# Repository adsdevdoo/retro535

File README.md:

# retro535

**Siemens SAB80535-N Retro Development Board v1.0** — плата 100 × 80 мм,
два слоя, съёмный SAB80535-N в THT-панели PLCC-68, 64 КиБ доступного CODE
во внешней Flash и отдельные 32 КиБ SRAM. Питание USB-C; FT232RL UART,
RESET, пользовательский LED P4.0, разъёмы GPIO/аналоговых входов/шины.

**Статус: инженерный прототип, не испытан в железе.** Производственный архив
для первой пробной партии — `fabrication/retro535-v1.0-jlcpcb.zip`.
Контрольные результаты и границы проверки — `reports/release-review.md`.
Покупку, загрузку файлов и заказ в JLCPCB выполняет владелец платы.

## Открыть проект

Открыть `hardware/retro535.kicad_pro` в **KiCad 9.0.2 или новее**.
Главная схема `retro535.kicad_sch` включает ещё три редактируемых листа.
Плата `retro535.kicad_pcb` полностью разведена. Локальные символы,
footprints и 3D находятся рядом; сохранять структуру каталогов.

- [Архитектура, карта памяти, уровни и временной бюджет](docs/architecture.md)
- [Распиновка МК, разъёмов и контрольных точек](docs/pinout.md)
- [Сборка, первая прошивка и первое включение](docs/bring-up.md)
- [Параметры заказа JLCPCB](docs/manufacturing.md)
- [BOM с артикулами](docs/BOM.csv)
- [Схема PDF](docs/schematic.pdf)
- [Прошивка, сборка и бесплатная симуляция](firmware/README.md)
- [Datasheet и источники](docs/sources.md)
- [3D-модели и их ограничения](docs/models.md)

## Перед заказом и включением

МК ROMless: встроенного UART-загрузчика нет. USB-UART **не программатор**.
Первую прошивку и все обновления v1.0 записывают внешним программатором
в снятую SST39SF010A при полностью отключённой плате. Flash WE# на плате
заблокирован высоким уровнем; верхние 64 КиБ её 128-КиБ массива не используются.

JP1 сначала открыт: FT_PROG должен настроить USB bus-powered 500 mA,
CBUS3=PWREN# и pull-down on suspend. Основная часть включается после
enumeration; от зарядки без USB-хоста автономного старта нет. Под нагрузкой
нужно **>4,75 В на TP3**; слабый порт/длинный кабель может оставить МК в RESET.
GPIO — 5 В TTL. Периферию не подключать до успешного теста SRAM.

## Проверки и воспроизводимость

Схема создана из `tools/design.py`; `tools/generate.py` обновляет схему,
BOM и правила проекта, сохраняя отредактированную локальную библиотеку.
**Не запускать make_board.py/finish_board.py/polish_board.py на финальном
PCB:** это этапы построения, они могут затереть готовую разводку.
Для новой разводки использовать отдельную копию проекта.

`tools/sync_board_metadata.py` назначает служебные NC-цепи из актуального
`reports/netlist.xml` и синхронизирует библиотеку с проверенной геометрией.
`tools/audit_models.py` проверяет все файлы 3D. `tools/audit_manufacturing.py`
независимо проверяет Gerber/Drill и собирает ZIP; ему нужен `gerbonara`
и свежий `reports/pcb-geometry.json` из `tools/export_geometry.py` (KiCad Python). CLI KiCad, работающие с одним проектом,
запускать последовательно: они могут сохранять настройки даже при экспорте.

3D-рендеры показывают пустые панели U1/U3/U4. Панель PLCC и F1 — условные
модели; внешность не доказывает точную механику. На PCB присутствуют все
68 контактов U1 независимо от упрощений STEP.

GitHub: [adsdevdoo/retro535](https://github.com/adsdevdoo/retro535).
Инструкция SSH/plink для этой Windows-машины сохранена в `AGENTS.md`.
Сторонние 3D-модели сохраняют собственные лицензии; см. `docs/models.md`.

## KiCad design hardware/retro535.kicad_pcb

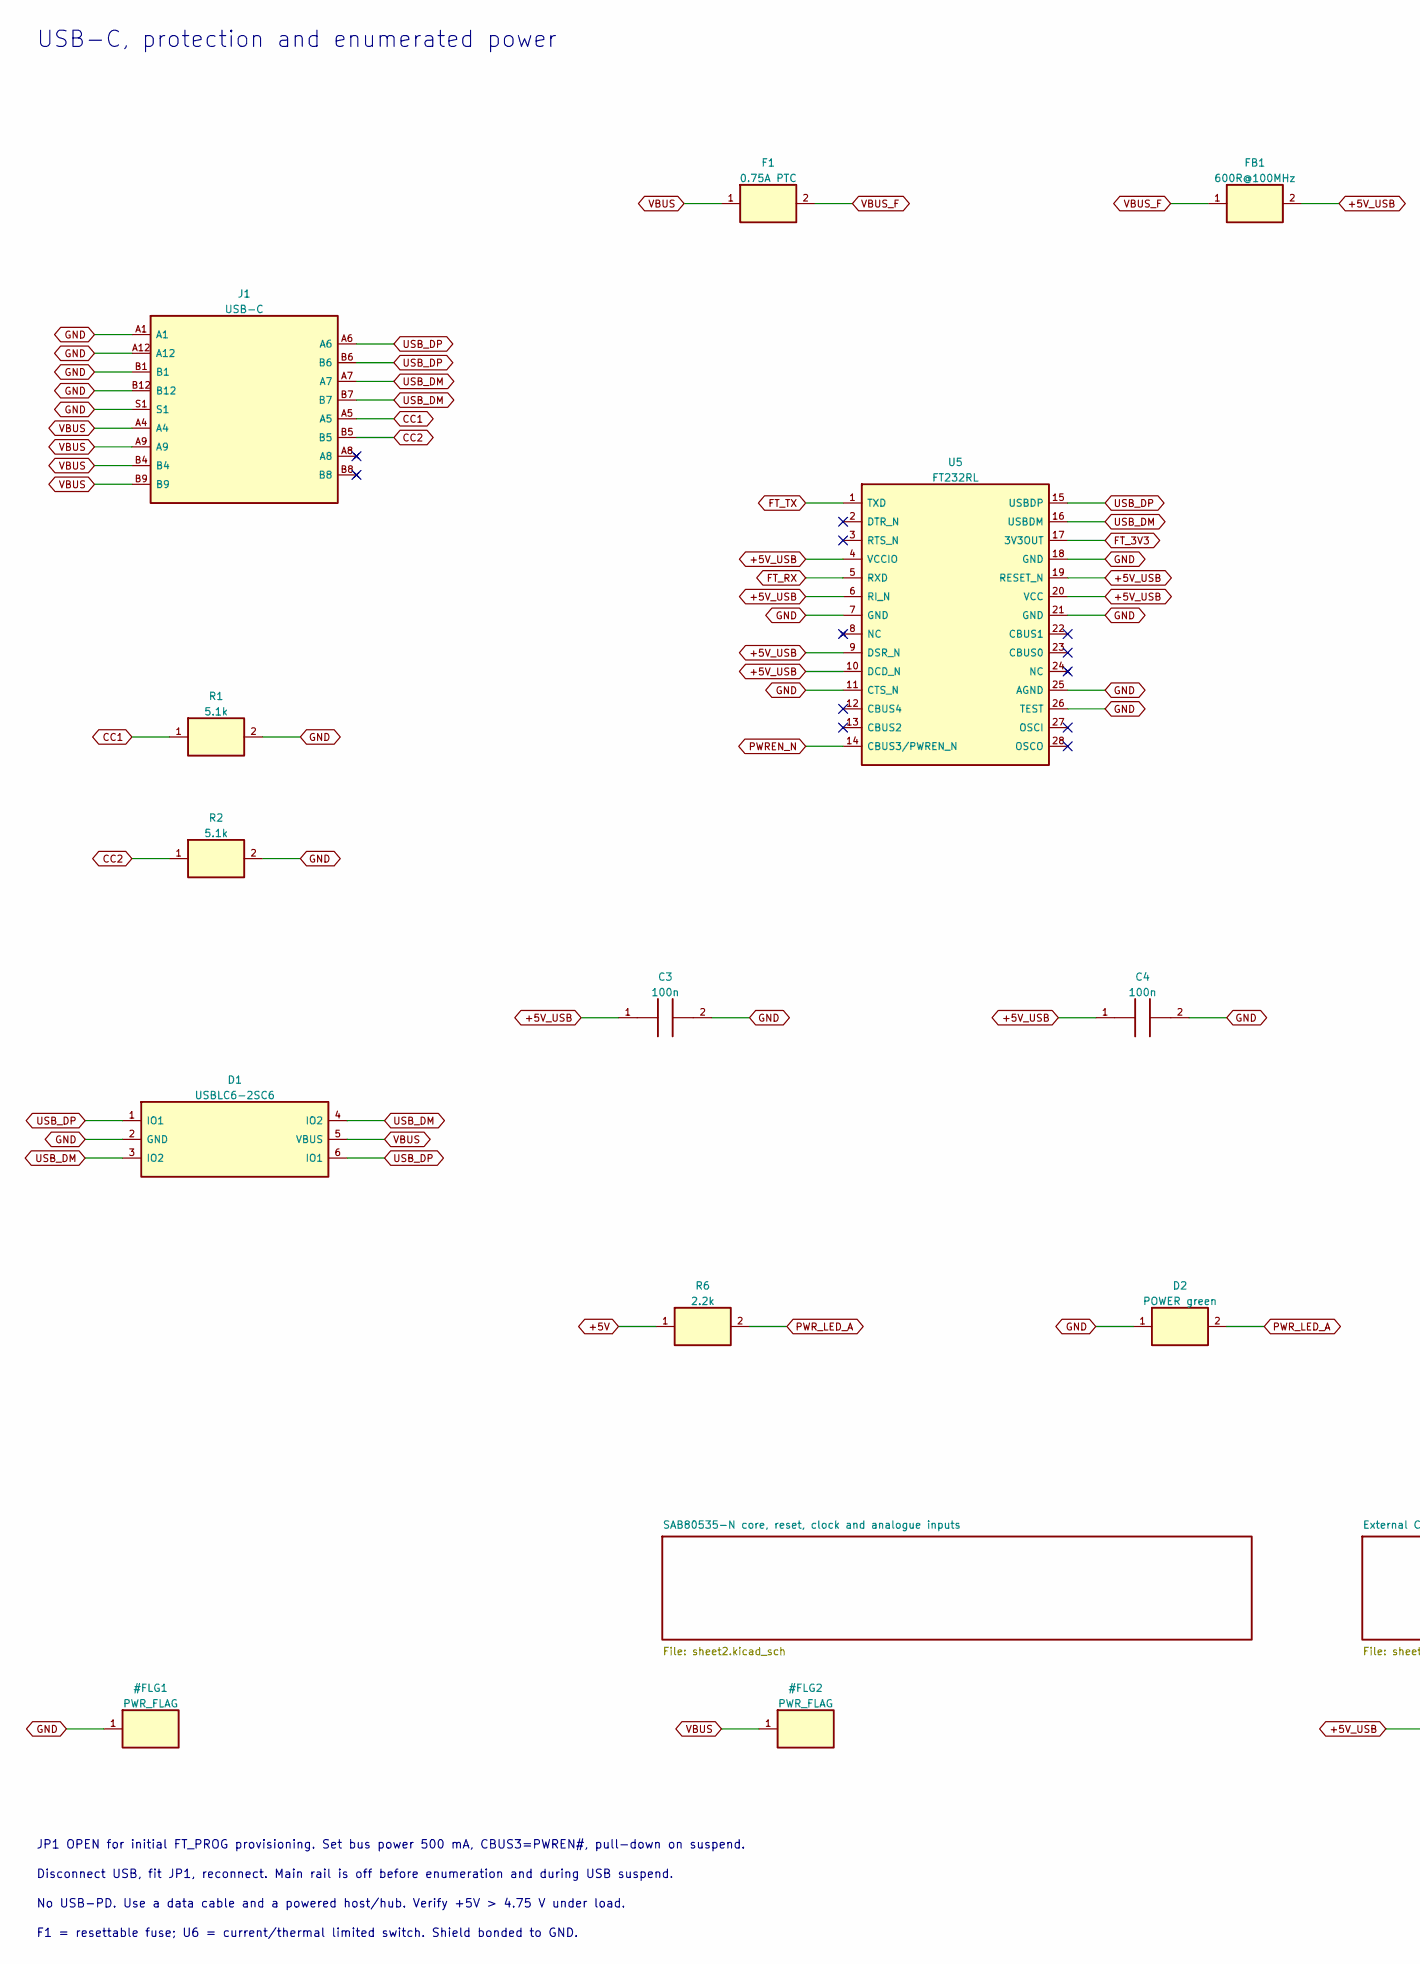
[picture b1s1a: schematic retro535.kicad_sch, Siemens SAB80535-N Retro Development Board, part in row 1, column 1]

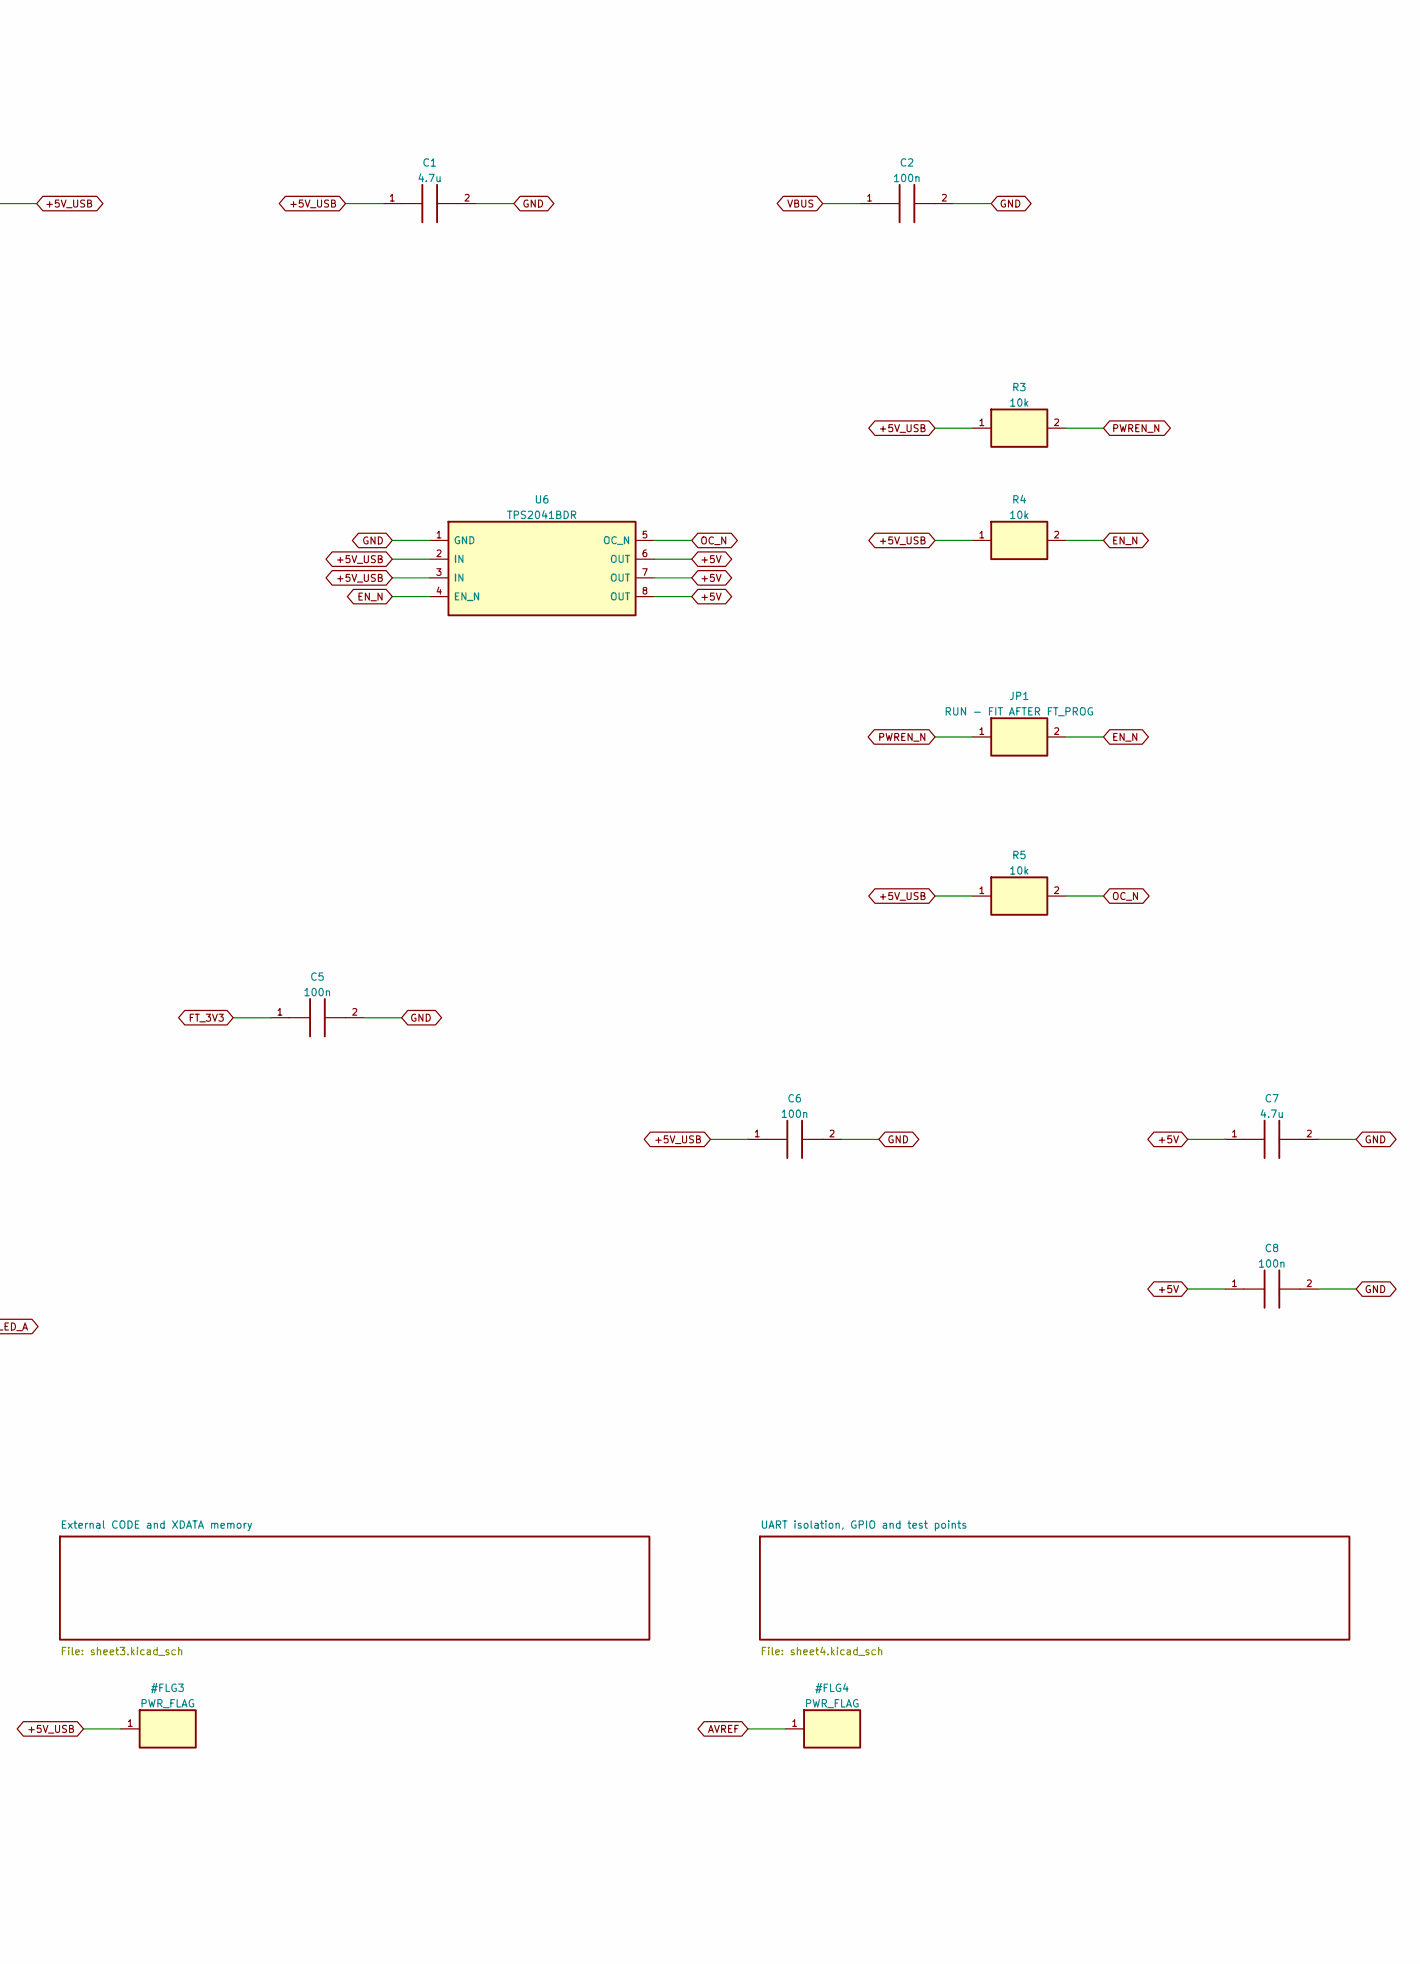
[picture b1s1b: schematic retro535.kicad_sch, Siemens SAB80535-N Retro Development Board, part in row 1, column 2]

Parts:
C1, C7: 4.7u; C_0805_2012Metric_Pad1.18x1.45mm_HandSolder; MPN GRM21BR61C475KA73L
C2, C3, C4, C5, C6, C8: 100n; C_0805_2012Metric_Pad1.18x1.45mm_HandSolder; MPN GRM21BR71H104KA01L
D1: USBLC6-2SC6; SOT-23-6; MPN USBLC6-2SC6
D2: POWER green; LED_0805_2012Metric_Pad1.15x1.40mm_HandSolder; MPN LTST-C170KGKT
F1: 0.75A PTC; Fuse_1812_4532Metric; MPN MF-MSMF075-2
FB1: 600R@100MHz; L_0805_2012Metric_Pad1.15x1.40mm_HandSolder; MPN BLM21PG601SN1D
J1: USB-C; USB_C_Receptacle_HRO_TYPE-C-31-M-12; MPN TYPE-C-31-M-12
JP1: RUN - FIT AFTER FT_PROG; PinHeader_1x02_P2.54mm_Vertical; MPN M20-9990245
R1, R2: 5.1k; R_0805_2012Metric_Pad1.20x1.40mm_HandSolder; MPN RC0805FR-075K1L
R3, R4, R5: 10k; R_0805_2012Metric_Pad1.20x1.40mm_HandSolder; MPN RC0805FR-0710KL
R6: 2.2k; R_0805_2012Metric_Pad1.20x1.40mm_HandSolder; MPN RC0805FR-072K2L
U5: FT232RL; SSOP-28_5.3x10.2mm_P0.65mm; MPN FT232RL
U6: TPS2041BDR; SOIC-8_3.9x4.9mm_P1.27mm; MPN TPS2041BDR

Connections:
+5V: C7.1, C8.1, R6.1, U6.6 (OUT), U6.7 (OUT), U6.8 (OUT); also elsewhere on the board
+5V_USB: C1.1, C3.1, C4.1, C6.1, FB1.2, R3.1, R4.1, R5.1, U5.4 (VCCIO), U5.6 (RI_N), U5.9 (DSR_N), U5.10 (DCD_N), U5.19 (RESET_N), U5.20 (VCC), U6.2 (IN), U6.3 (IN); also elsewhere on the board
CC1: J1.A5, R1.1
CC2: J1.B5, R2.1
EN_N: JP1.2, R4.2, U6.4 (EN_N)
FT_3V3: C5.1, U5.17 (3V3OUT)
FT_RX: U5.5 (RXD); also elsewhere on the board
FT_TX: U5.1 (TXD); also elsewhere on the board
GND: C1.2, C2.2, C3.2, C4.2, C5.2, C6.2, C7.2, C8.2, D1.2 (GND), D2.1, J1.A1, J1.A12, J1.B1, J1.B12, J1.S1, R1.2, R2.2, U5.7 (GND), U5.11 (CTS_N), U5.18 (GND), U5.21 (GND), U5.25 (AGND), U5.26 (TEST), U6.1 (GND); also elsewhere on the board
OC_N: R5.2, U6.5 (OC_N); also elsewhere on the board
PWREN_N: JP1.1, R3.2, U5.14 (CBUS3/PWREN_N)
PWR_LED_A: D2.2, R6.2
USB_DM: D1.3 (IO2), D1.4 (IO2), J1.A7, J1.B7, U5.16 (USBDM)
USB_DP: D1.1 (IO1), D1.6 (IO1), J1.A6, J1.B6, U5.15 (USBDP)
VBUS: C2.1, D1.5 (VBUS), F1.1, J1.A4, J1.A9, J1.B4, J1.B9
VBUS_F: F1.2, FB1.1

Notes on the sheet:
USB-C, protection and enumerated power
JP1 OPEN for initial FT_PROG provisioning. Set bus power 500 mA, CBUS3=PWREN#, pull-down on suspend.
Disconnect USB, fit JP1, reconnect. Main rail is off before enumeration and during USB suspend.
No USB-PD. Use a data cable and a powered host/hub. Verify +5V > 4.75 V under load.
F1 = resettable fuse; U6 = current/thermal limited switch. Shield bonded to GND.

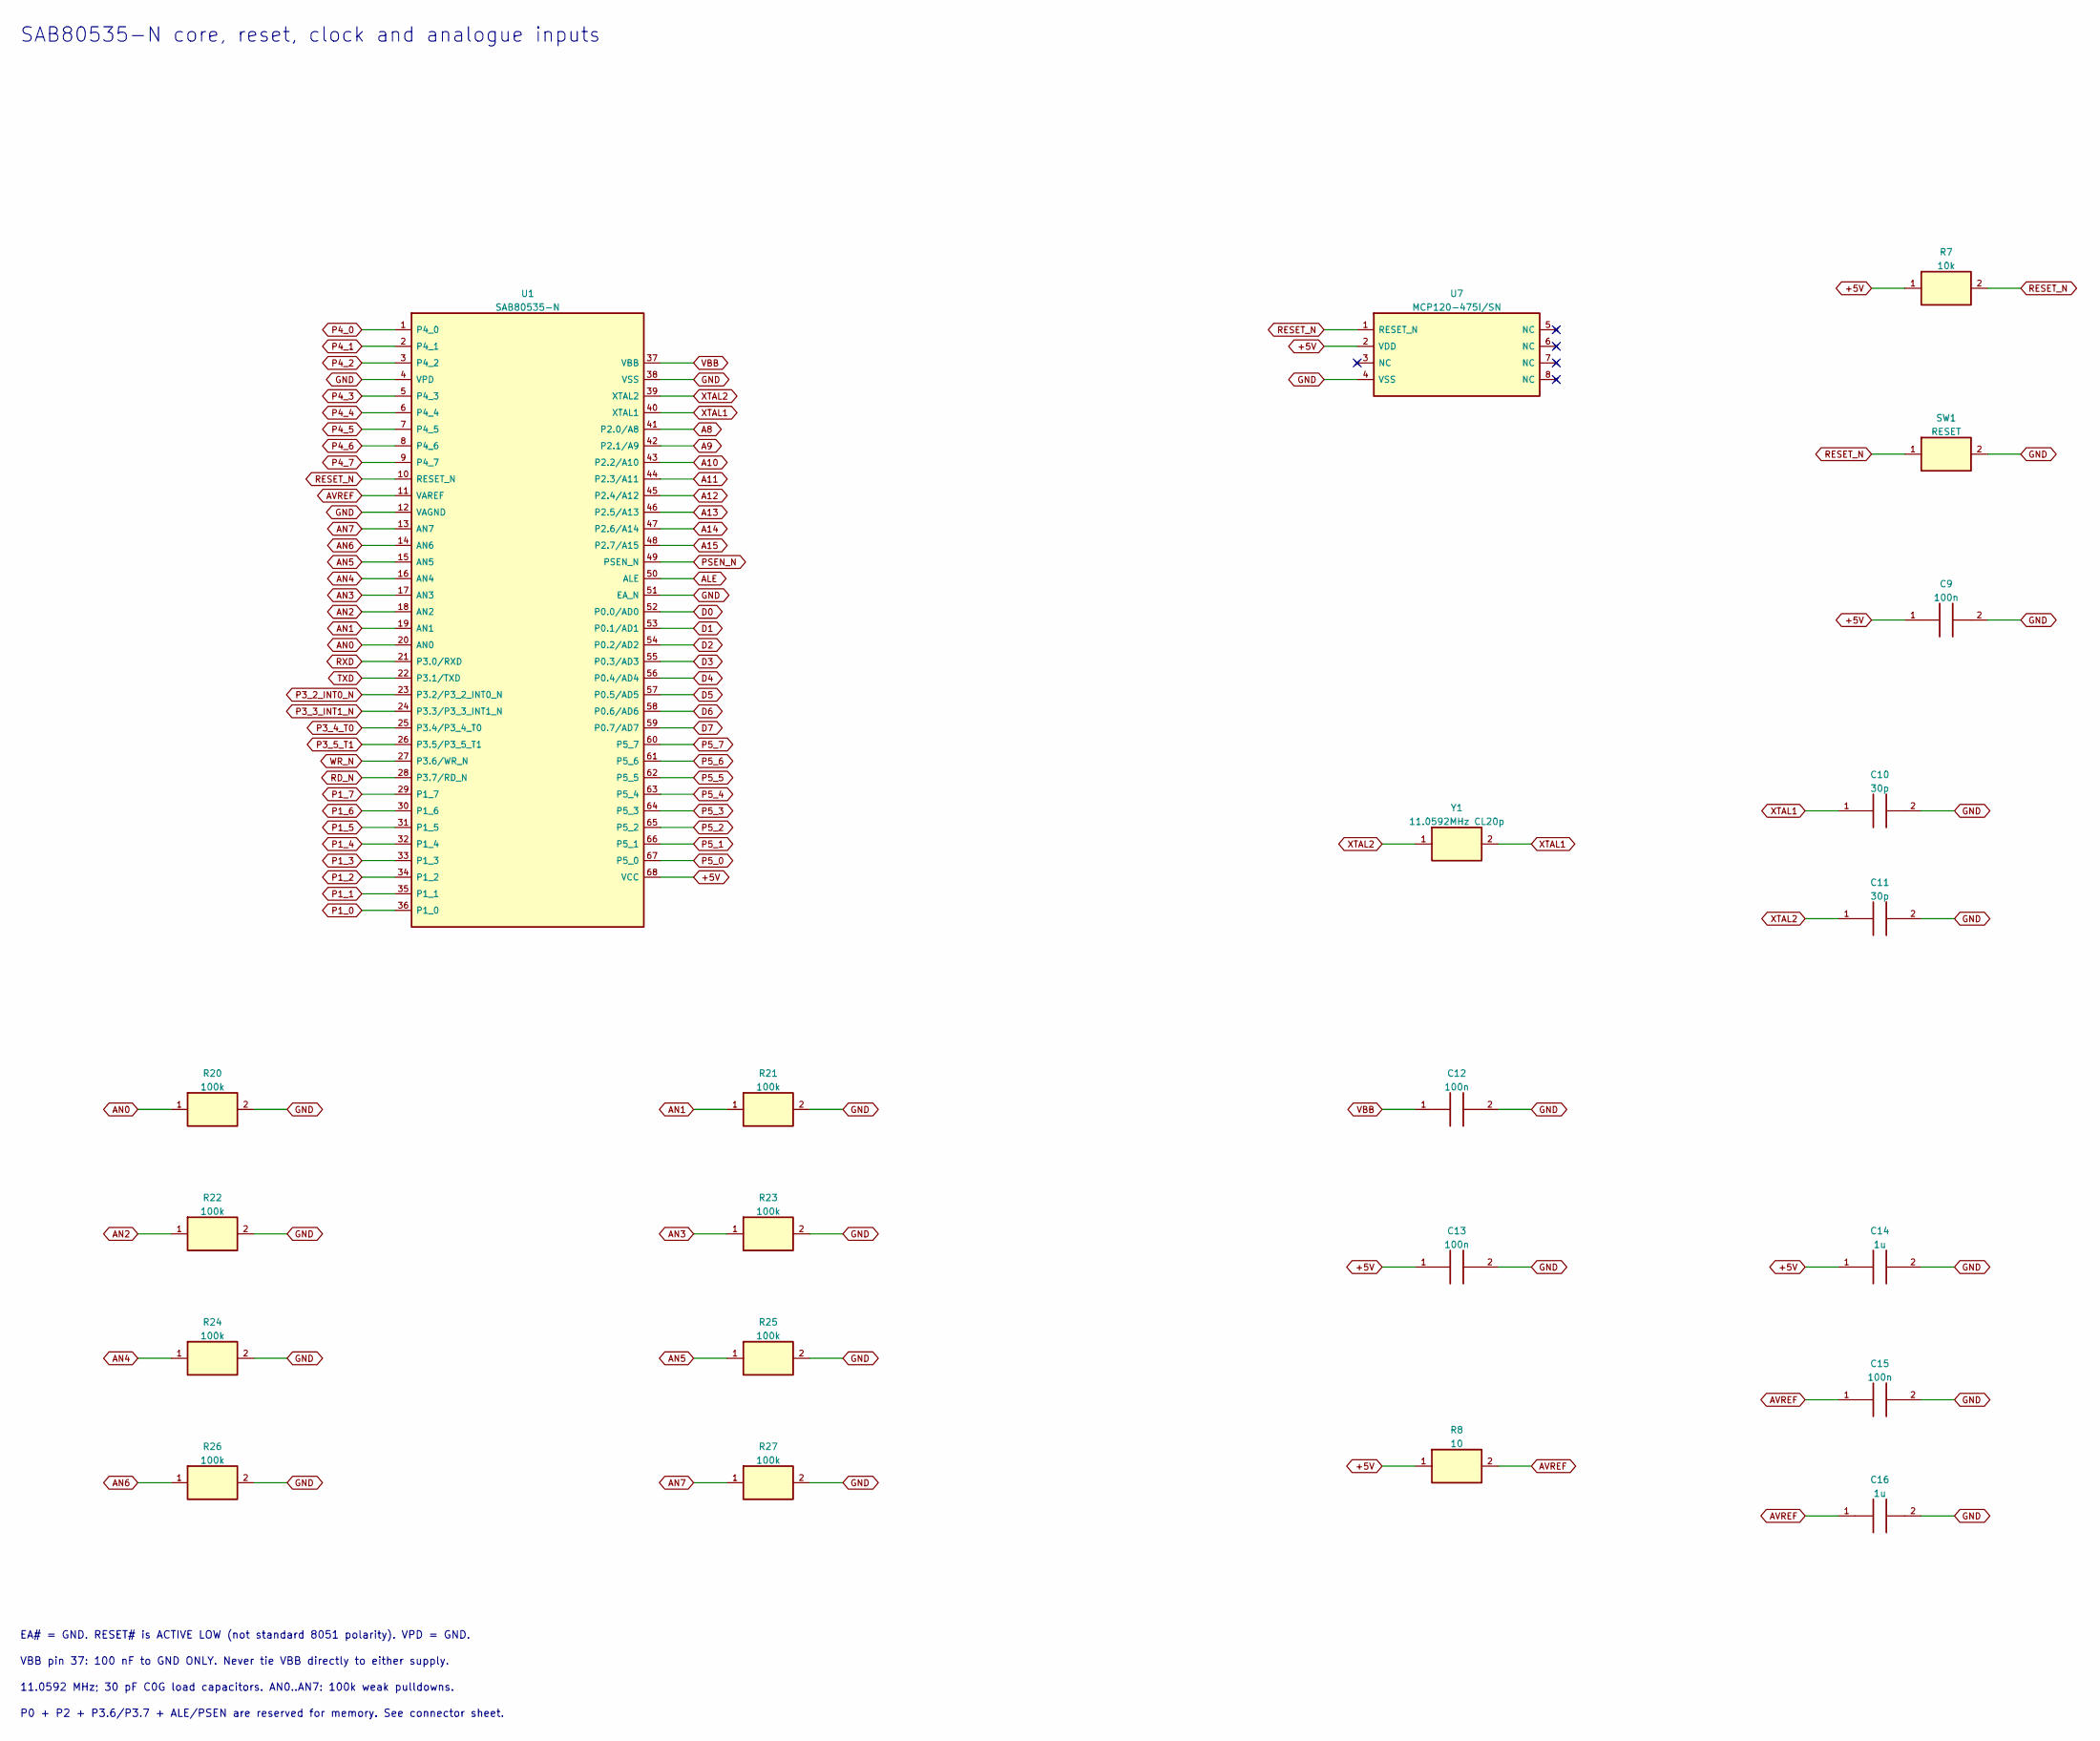
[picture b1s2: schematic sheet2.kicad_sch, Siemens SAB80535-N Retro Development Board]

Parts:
C9, C12, C13, C15: 100n; C_0805_2012Metric_Pad1.18x1.45mm_HandSolder; MPN GRM21BR71H104KA01L
C10, C11: 30p; C_0805_2012Metric_Pad1.18x1.45mm_HandSolder; MPN GRM2165C1H300JA01D
C14, C16: 1u; C_0805_2012Metric_Pad1.18x1.45mm_HandSolder; MPN GRM21BR71C105KA01L
R7: 10k; R_0805_2012Metric_Pad1.20x1.40mm_HandSolder; MPN RC0805FR-0710KL
R8: 10; R_0805_2012Metric_Pad1.20x1.40mm_HandSolder; MPN RC0805FR-0710RL
R20, R21, R22, R23, R24, R25, R26, R27: 100k; R_0805_2012Metric_Pad1.20x1.40mm_HandSolder; MPN RC0805FR-07100KL
SW1: RESET; SW_PUSH_6mm; MPN B3F-1000
U1: SAB80535-N; PLCC68_PreciDip_540-99-068-24-000-1; MPN SAB80535-N
U7: MCP120-475I/SN; SOIC-8_3.9x4.9mm_P1.27mm; MPN MCP120-475I/SN
Y1: 11.0592MHz CL20p; Crystal_HC49-U_Vertical; MPN ECS-110.5-20-4X

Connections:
+5V: C9.1, C13.1, C14.1, R7.1, R8.1, U1.68 (VCC), U7.2 (VDD); also elsewhere on the board
A8: U1.41 (P2.0/A8); also elsewhere on the board
A9: U1.42 (P2.1/A9); also elsewhere on the board
A10: U1.43 (P2.2/A10); also elsewhere on the board
A11: U1.44 (P2.3/A11); also elsewhere on the board
A12: U1.45 (P2.4/A12); also elsewhere on the board
A13: U1.46 (P2.5/A13); also elsewhere on the board
A14: U1.47 (P2.6/A14); also elsewhere on the board
A15: U1.48 (P2.7/A15); also elsewhere on the board
ALE: U1.50 (ALE); also elsewhere on the board
AN0: R20.1, U1.20 (AN0); also elsewhere on the board
AN1: R21.1, U1.19 (AN1); also elsewhere on the board
AN2: R22.1, U1.18 (AN2); also elsewhere on the board
AN3: R23.1, U1.17 (AN3); also elsewhere on the board
AN4: R24.1, U1.16 (AN4); also elsewhere on the board
AN5: R25.1, U1.15 (AN5); also elsewhere on the board
AN6: R26.1, U1.14 (AN6); also elsewhere on the board
AN7: R27.1, U1.13 (AN7); also elsewhere on the board
AVREF: C15.1, C16.1, R8.2, U1.11 (VAREF); also elsewhere on the board
D0: U1.52 (P0.0/AD0); also elsewhere on the board
D1: U1.53 (P0.1/AD1); also elsewhere on the board
D2: U1.54 (P0.2/AD2); also elsewhere on the board
D3: U1.55 (P0.3/AD3); also elsewhere on the board
D4: U1.56 (P0.4/AD4); also elsewhere on the board
D5: U1.57 (P0.5/AD5); also elsewhere on the board
D6: U1.58 (P0.6/AD6); also elsewhere on the board
D7: U1.59 (P0.7/AD7); also elsewhere on the board
GND: C9.2, C10.2, C11.2, C12.2, C13.2, C14.2, C15.2, C16.2, R20.2, R21.2, R22.2, R23.2, R24.2, R25.2, R26.2, R27.2, SW1.2, U1.4 (VPD), U1.12 (VAGND), U1.38 (VSS), U1.51 (EA_N), U7.4 (VSS); also elsewhere on the board
P1_0: U1.36 (P1_0); also elsewhere on the board
P1_1: U1.35 (P1_1); also elsewhere on the board
P1_2: U1.34 (P1_2); also elsewhere on the board
P1_3: U1.33 (P1_3); also elsewhere on the board
P1_4: U1.32 (P1_4); also elsewhere on the board
P1_5: U1.31 (P1_5); also elsewhere on the board
P1_6: U1.30 (P1_6); also elsewhere on the board
P1_7: U1.29 (P1_7); also elsewhere on the board
P3_2_INT0_N: U1.23 (P3.2/P3_2_INT0_N); also elsewhere on the board
P3_3_INT1_N: U1.24 (P3.3/P3_3_INT1_N); also elsewhere on the board
P3_4_T0: U1.25 (P3.4/P3_4_T0); also elsewhere on the board
P3_5_T1: U1.26 (P3.5/P3_5_T1); also elsewhere on the board
P4_0: U1.1 (P4_0); also elsewhere on the board
P4_1: U1.2 (P4_1); also elsewhere on the board
P4_2: U1.3 (P4_2); also elsewhere on the board
P4_3: U1.5 (P4_3); also elsewhere on the board
P4_4: U1.6 (P4_4); also elsewhere on the board
P4_5: U1.7 (P4_5); also elsewhere on the board
P4_6: U1.8 (P4_6); also elsewhere on the board
P4_7: U1.9 (P4_7); also elsewhere on the board
P5_0: U1.67 (P5_0); also elsewhere on the board
P5_1: U1.66 (P5_1); also elsewhere on the board
P5_2: U1.65 (P5_2); also elsewhere on the board
P5_3: U1.64 (P5_3); also elsewhere on the board
P5_4: U1.63 (P5_4); also elsewhere on the board
P5_5: U1.62 (P5_5); also elsewhere on the board
P5_6: U1.61 (P5_6); also elsewhere on the board
P5_7: U1.60 (P5_7); also elsewhere on the board
PSEN_N: U1.49 (PSEN_N); also elsewhere on the board
RD_N: U1.28 (P3.7/RD_N); also elsewhere on the board
RESET_N: R7.2, SW1.1, U1.10 (RESET_N), U7.1 (RESET_N); also elsewhere on the board
RXD: U1.21 (P3.0/RXD); also elsewhere on the board
TXD: U1.22 (P3.1/TXD); also elsewhere on the board
VBB: C12.1, U1.37 (VBB)
WR_N: U1.27 (P3.6/WR_N); also elsewhere on the board
XTAL1: C10.1, U1.40 (XTAL1), Y1.2
XTAL2: C11.1, U1.39 (XTAL2), Y1.1

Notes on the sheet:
SAB80535-N core, reset, clock and analogue inputs
EA# = GND. RESET# is ACTIVE LOW (not standard 8051 polarity). VPD = GND.
VBB pin 37: 100 nF to GND ONLY. Never tie VBB directly to either supply.
11.0592 MHz; 30 pF C0G load capacitors. AN0..AN7: 100k weak pulldowns.
P0 + P2 + P3.6/P3.7 + ALE/PSEN are reserved for memory. See connector sheet.

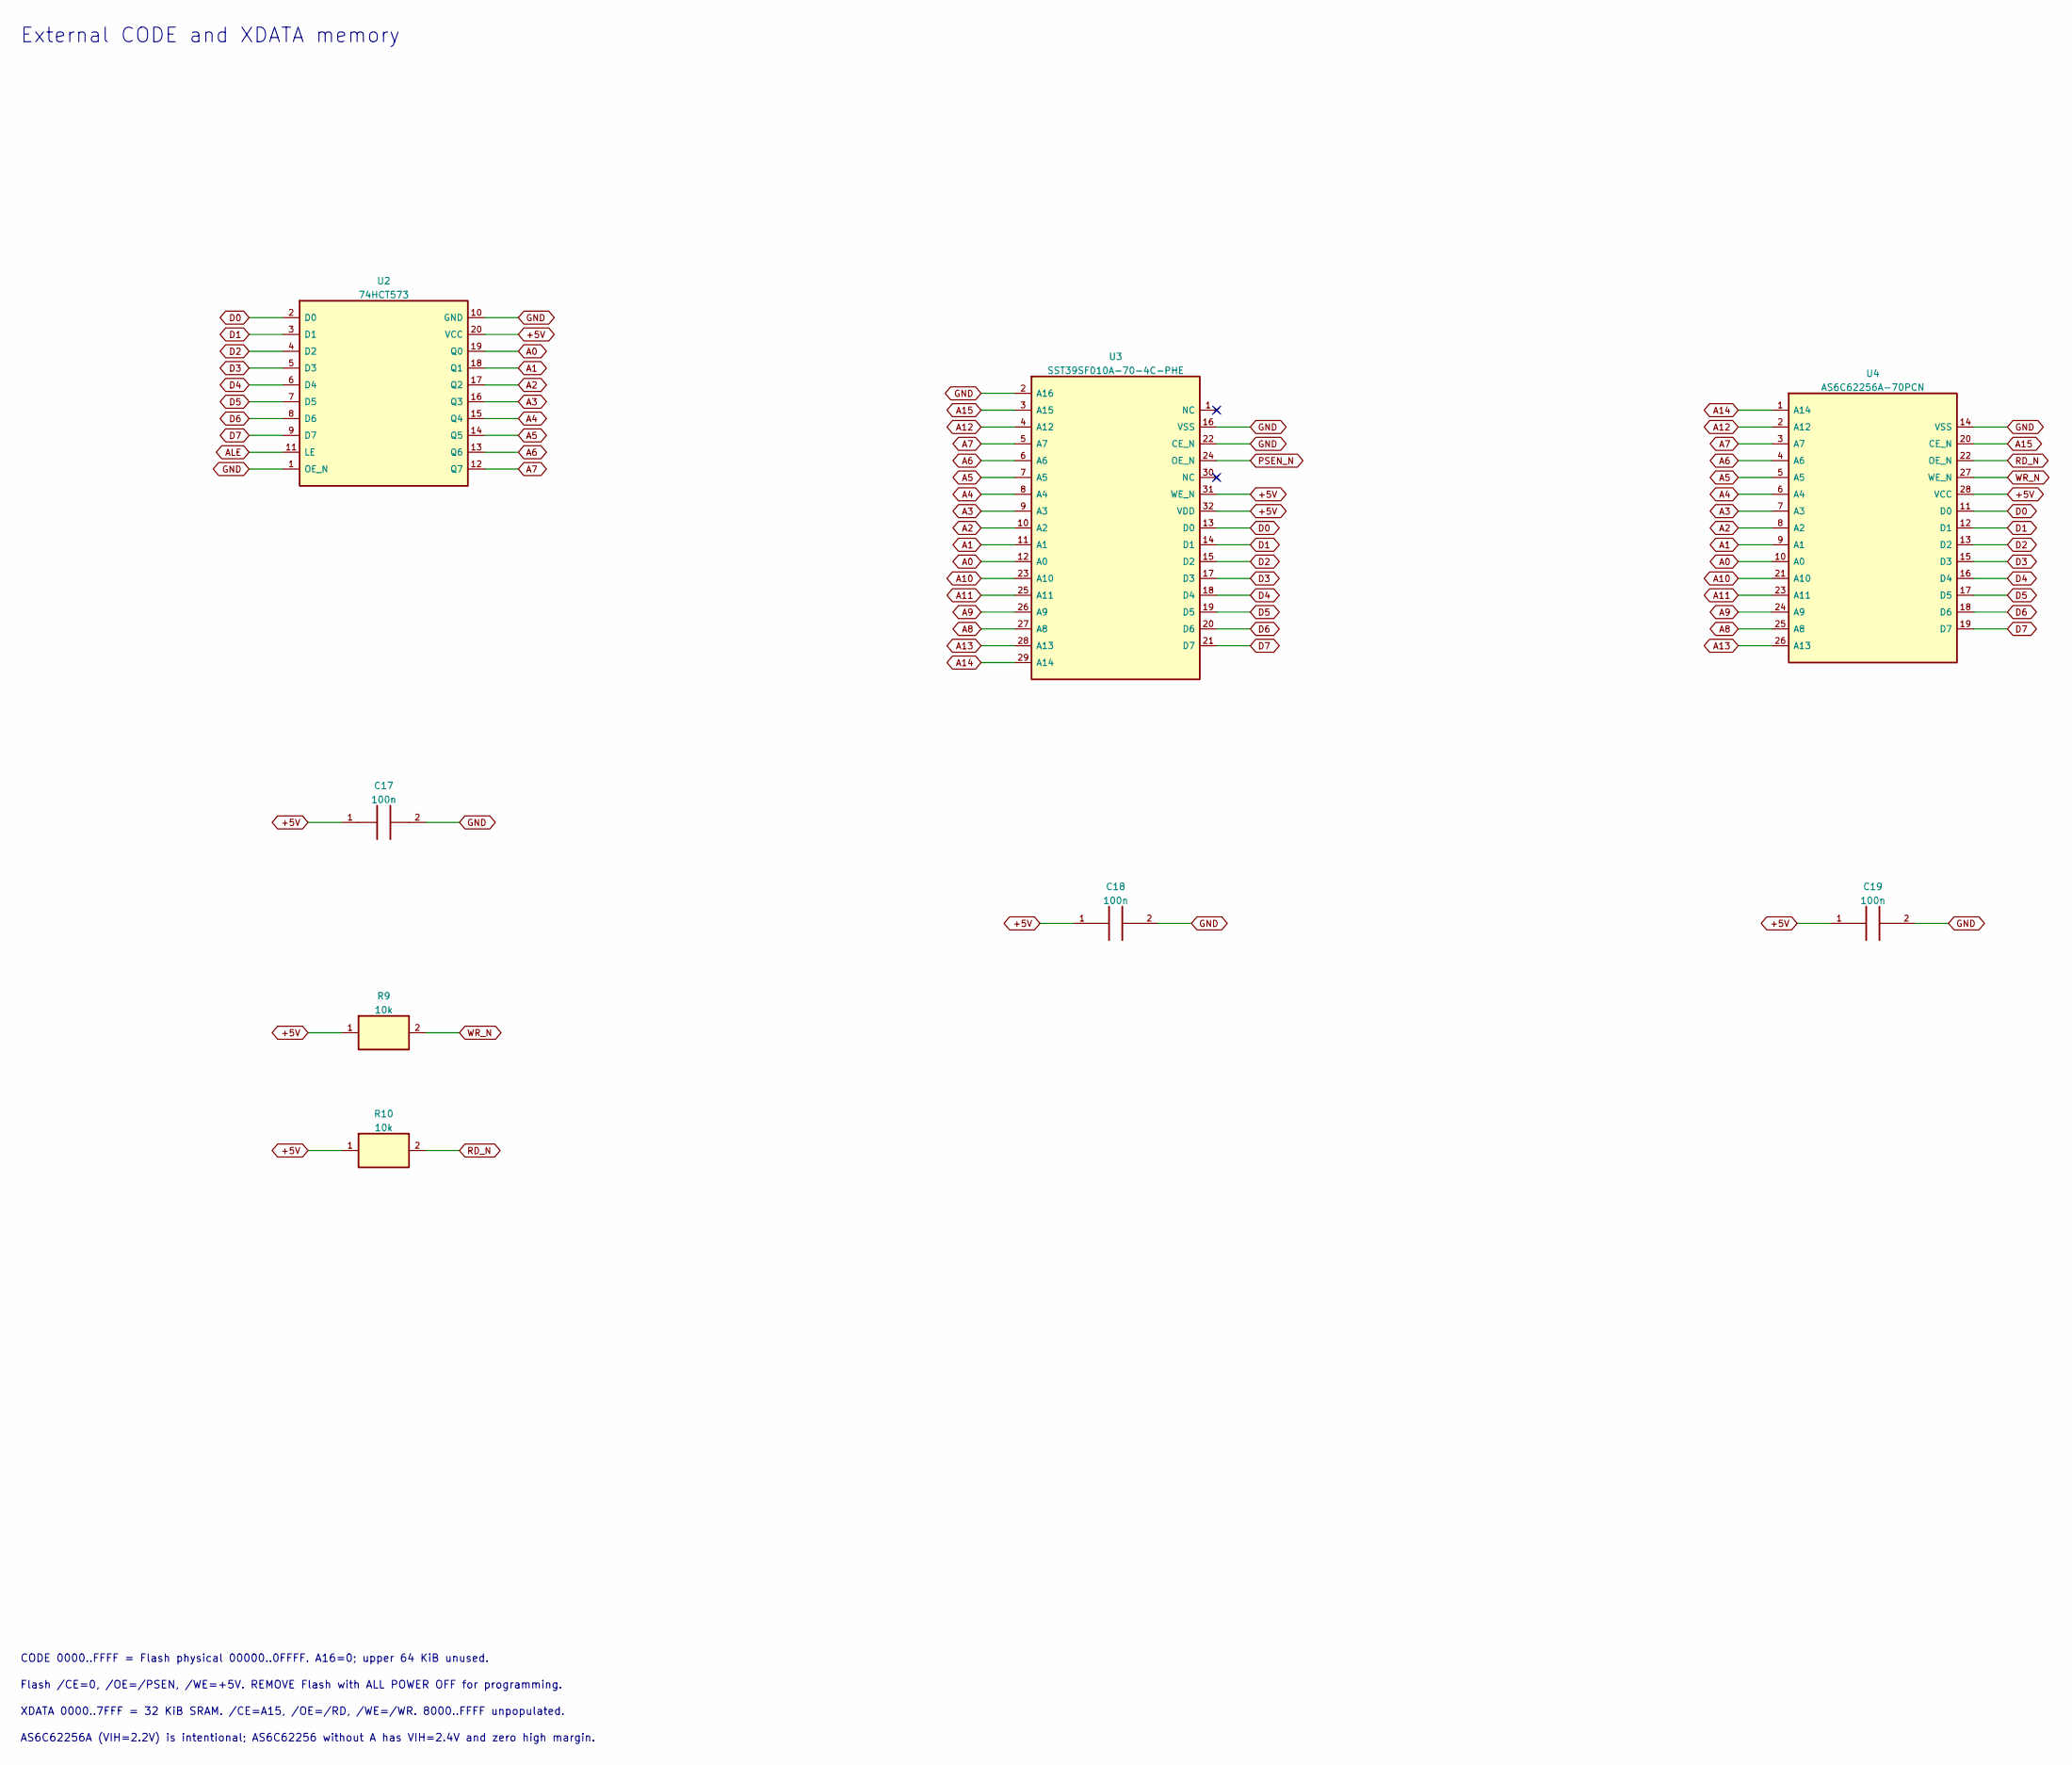
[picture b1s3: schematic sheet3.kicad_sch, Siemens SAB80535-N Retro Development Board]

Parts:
C17, C18, C19: 100n; C_0805_2012Metric_Pad1.18x1.45mm_HandSolder; MPN GRM21BR71H104KA01L
R9, R10: 10k; R_0805_2012Metric_Pad1.20x1.40mm_HandSolder; MPN RC0805FR-0710KL
U2: 74HCT573; SOIC-20W_7.5x12.8mm_P1.27mm; MPN SN74HCT573DWR
U3: SST39SF010A-70-4C-PHE; DIP-32_W15.24mm_Socket_LongPads; MPN SST39SF010A-70-4C-PHE
U4: AS6C62256A-70PCN; DIP-28_W15.24mm_Socket_LongPads; MPN AS6C62256A-70PCN

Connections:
+5V: C17.1, C18.1, C19.1, R9.1, R10.1, U2.20 (VCC), U3.31 (WE_N), U3.32 (VDD), U4.28 (VCC); also elsewhere on the board
A0: U2.19 (Q0), U3.12 (A0), U4.10 (A0); also elsewhere on the board
A1: U2.18 (Q1), U3.11 (A1), U4.9 (A1); also elsewhere on the board
A2: U2.17 (Q2), U3.10 (A2), U4.8 (A2); also elsewhere on the board
A3: U2.16 (Q3), U3.9 (A3), U4.7 (A3); also elsewhere on the board
A4: U2.15 (Q4), U3.8 (A4), U4.6 (A4); also elsewhere on the board
A5: U2.14 (Q5), U3.7 (A5), U4.5 (A5); also elsewhere on the board
A6: U2.13 (Q6), U3.6 (A6), U4.4 (A6); also elsewhere on the board
A7: U2.12 (Q7), U3.5 (A7), U4.3 (A7); also elsewhere on the board
A8: U3.27 (A8), U4.25 (A8); also elsewhere on the board
A9: U3.26 (A9), U4.24 (A9); also elsewhere on the board
A10: U3.23 (A10), U4.21 (A10); also elsewhere on the board
A11: U3.25 (A11), U4.23 (A11); also elsewhere on the board
A12: U3.4 (A12), U4.2 (A12); also elsewhere on the board
A13: U3.28 (A13), U4.26 (A13); also elsewhere on the board
A14: U3.29 (A14), U4.1 (A14); also elsewhere on the board
A15: U3.3 (A15), U4.20 (CE_N); also elsewhere on the board
ALE: U2.11 (LE); also elsewhere on the board
D0: U2.2 (D0), U3.13 (D0), U4.11 (D0); also elsewhere on the board
D1: U2.3 (D1), U3.14 (D1), U4.12 (D1); also elsewhere on the board
D2: U2.4 (D2), U3.15 (D2), U4.13 (D2); also elsewhere on the board
D3: U2.5 (D3), U3.17 (D3), U4.15 (D3); also elsewhere on the board
D4: U2.6 (D4), U3.18 (D4), U4.16 (D4); also elsewhere on the board
D5: U2.7 (D5), U3.19 (D5), U4.17 (D5); also elsewhere on the board
D6: U2.8 (D6), U3.20 (D6), U4.18 (D6); also elsewhere on the board
D7: U2.9 (D7), U3.21 (D7), U4.19 (D7); also elsewhere on the board
GND: C17.2, C18.2, C19.2, U2.1 (OE_N), U2.10 (GND), U3.2 (A16), U3.16 (VSS), U3.22 (CE_N), U4.14 (VSS); also elsewhere on the board
PSEN_N: U3.24 (OE_N); also elsewhere on the board
RD_N: R10.2, U4.22 (OE_N); also elsewhere on the board
WR_N: R9.2, U4.27 (WE_N); also elsewhere on the board

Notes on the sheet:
External CODE and XDATA memory
CODE 0000..FFFF = Flash physical 00000..0FFFF. A16=0; upper 64 KiB unused.
Flash /CE=0, /OE=/PSEN, /WE=+5V. REMOVE Flash with ALL POWER OFF for programming.
XDATA 0000..7FFF = 32 KiB SRAM. /CE=A15, /OE=/RD, /WE=/WR. 8000..FFFF unpopulated.
AS6C62256A (VIH=2.2V) is intentional; AS6C62256 without A has VIH=2.4V and zero high margin.
